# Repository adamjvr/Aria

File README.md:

# Aria
ARM Cortex M4F + WiFi + MPPT Solar Battery Powered module, mBed and Arduino Compatible hardware development platform.
- ARM Cortex M4F 180MHZ STM32F446RET6
- ESP8285 WiFi SoC w/ PCB Antenna
- WiFi
- USB 2.0 Connectivity
- Plenty or GPIO/Serial via the STM32
- Over the air programming and updating
- Lithium Ion Battery Power
- MPPT Solar battery charging
- USB bus power for desktop development
- Over the Air Programming
- Low power
- 2 Year Battery Life w/Single Cell Lithium Battery

Aria 0.1a PCB

Aria 0.1a 3D Render of PCB
Top

Bottom

Aria 0.1a ESP-12E Version PCB

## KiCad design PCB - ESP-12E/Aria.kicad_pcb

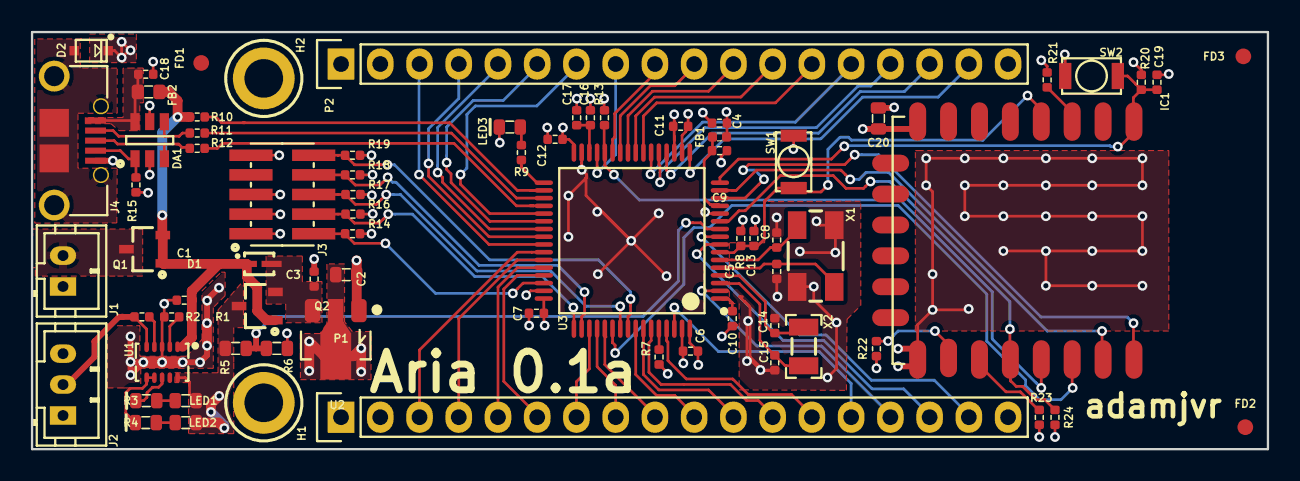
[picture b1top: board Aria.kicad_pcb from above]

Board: 4 copper layers, 80.0 x 27.0 mm, 73 parts (0 on the bottom side), 76 nets.

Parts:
C1, C2: CL05A105KA5NQNC; C0402
C3, C20: CL10A106KQ8NNNC; C0603
C4, C6, C7, C9, C10, C11, C12, C13, C17, C18, C19: CL05B104JP5NNNC; C0402
C5, C8: CL05C090CB5NNNC; C0402
C14, C15: CL05C180GB5NCNC; C0402
C16: CL05A475KQ5NRNC; C0402
D1: BAT20JFILM
D2: RSB39VTE-17
DA1: ESDA6V1BC6
FB1: BLM15HG601SN1D
FB2: MI0603K300R-10
FD1, FD2, FD3: FIDUCIAL
H1, H2: M2.5_Hole; M2.5_HOLE
IC1: ESP_12E; ESP-12E
J1: B2B-PH-K-S(LF)(SN)
J2: B3B-PH-K-S(LF)(SN)
J3: 20021121-00010C4LF
J4: 0475890001-MicroUSBPort; 0475890001
LED1: LTST-C191KGKT; LED0603
LED2: LTST-C191KFKT; LED0603
LED3: LTST-C193TBKT-5A; LED0603
P1, P2: CONN_01X18; Socket_Strip_Straight_1x18
Q1, Q2: DMG2307L-7
R1: RC1005F4870CS; R0402
R2, R8, R9, R14, R16, R17, R18, R19, R20: RC1005F102CS; R0402
R3, R4: RC1608J202CS; R0603
R5, R6: ERA-3AEB3741V; R0603
R7, R10, R13, R21, R22, R23, R24: RC1005F103CS; R0402
R11, R12: CPF0402B22RE1; R0402
R15: RC1005J473CS; R0402
SW1, SW2: B3U-1000P
U1: BQ24210DQCT; BQ24210
U2: AZ1117CR-3.3TRG1_1; AZ1117CR-3.3TRG1
U3: STM32F446RET6_-_TQFP64; STM32F446RET6
X1: ABM3B8.000MHZB2T
X2: ABS07-32.768KHZ-9-T

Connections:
+3V3: C3.1, C4.1, C6.1, C7.1, C10.1, C11.1, C12.1, C20.1, FB1.1, IC1.8, J3.1, P1.2, P2.2, R8.1, R13.1, R14.1, R16.1, R17.1, R18.1, R19.1, R20.1, R21.1, R23.1, R24.1, U2.2, U3.1, U3.19, U3.32, U3.48, U3.64
/MCU_STM32F446RET6/BAT_VOLT: R5.2, R6.1, U3.10
/MCU_STM32F446RET6/ESPTOST_BOOT0: IC1.20, U3.54
/MCU_STM32F446RET6/ESPTOST_BOOT1: IC1.19, R13.2, U3.28
/MCU_STM32F446RET6/ESP_PGM_MODE: IC1.18, R24.2, U3.11
/MCU_STM32F446RET6/ESP_ST_RST: C13.1, IC1.4, R8.2, SW1.1, U3.7
/MCU_STM32F446RET6/ESP_URX: IC1.22, U3.14
/MCU_STM32F446RET6/ESP_UTX: IC1.21, U3.15
/MCU_STM32F446RET6/HEARTBEAT: R9.1, U3.33
/MCU_STM32F446RET6/NJTRST: J3.10, R19.2, U3.56
/MCU_STM32F446RET6/PA3: P2.17, U3.17
/MCU_STM32F446RET6/PA4: P2.16, U3.20
/MCU_STM32F446RET6/PA5: P2.15, U3.21
/MCU_STM32F446RET6/PA6: P2.14, U3.22
/MCU_STM32F446RET6/PA7: P2.13, U3.23
/MCU_STM32F446RET6/PA8: P2.3, U3.41
/MCU_STM32F446RET6/PA9: P1.3, U3.42
/MCU_STM32F446RET6/PA10: P1.4, U3.43
/MCU_STM32F446RET6/PA11: P1.5, U3.44
/MCU_STM32F446RET6/PA12: P1.6, U3.45
/MCU_STM32F446RET6/PB0: P2.10, U3.26
/MCU_STM32F446RET6/PB1: P2.9, U3.27
/MCU_STM32F446RET6/PB5: P1.10, U3.57
/MCU_STM32F446RET6/PB6: P1.11, U3.58
/MCU_STM32F446RET6/PB7: P1.12, U3.59
/MCU_STM32F446RET6/PB8: P1.13, U3.61
/MCU_STM32F446RET6/PB9: P1.14, U3.62
/MCU_STM32F446RET6/PB10: P2.8, U3.29
/MCU_STM32F446RET6/PC0: P1.16, U3.8
/MCU_STM32F446RET6/PC1: P1.17, U3.9
/MCU_STM32F446RET6/PC4: P2.12, U3.24
/MCU_STM32F446RET6/PC5: P2.11, U3.25
/MCU_STM32F446RET6/PC6: P2.7, U3.37
/MCU_STM32F446RET6/PC7: P2.6, U3.38
/MCU_STM32F446RET6/PC8: P2.5, U3.39
/MCU_STM32F446RET6/PC9: P2.4, U3.40
/MCU_STM32F446RET6/PC10: P1.7, U3.51
/MCU_STM32F446RET6/PC11: P1.8, U3.52
/MCU_STM32F446RET6/PC12: P1.9, U3.53
/MCU_STM32F446RET6/PC13: P1.15, U3.2
/MCU_STM32F446RET6/STM_ESP_RST: C19.1, IC1.1, R20.2, SW2.2, U3.16
/MCU_STM32F446RET6/SWCLK_TCK: J3.4, R16.2, U3.49
/MCU_STM32F446RET6/SWDIO_TMS: J3.2, R14.2, U3.46
/MCU_STM32F446RET6/SWO_TDI: J3.8, R18.2, U3.50
/MCU_STM32F446RET6/SWO_TDO: J3.6, R17.2, U3.55
/MCU_STM32F446RET6/VBUS: C1.1, D1.1, FB2.1, Q1.1, Q1.2, Q2.1, R10.2, U1.1
/Power/BAT: J2.3, Q2.3, R3.2, R4.2, R5.1, U1.10
/Power/THERM: J2.2, R2.2, U1.5
GND: C1.2, C2.2, C3.2, C4.2, C5.2, C6.2, C7.2, C8.2, C9.2, C10.2, C11.2, C12.2, C13.2, C14.2, C15.2, C16.2, C17.2, C18.1, C19.2, C20.2, D2.2, DA1.2, DA1.5, IC1.15, J1.1, J2.1, J3.3, J3.5, J3.9, J4.5, LED3.2, P1.1, P1.18, P2.1, P2.18, R1.2, R6.2, R7.2, R15.2, R22.2, SW1.2, SW2.1, U1.3, U1.11, U2.1, U3.12, U3.18, U3.31, U3.47, U3.63, X1.2, X1.4
unnamed: C2.1, D1.2, Q2.2, U2.3
unnamed: C5.1, U3.5, X1.1
unnamed: C8.1, U3.6, X1.3
unnamed: C9.1, FB1.2, U3.13
unnamed: C14.1, U3.4, X2.1
unnamed: C15.1, U3.3, X2.2
unnamed: C16.1, C17.1, U3.30
unnamed: C18.2, DA1.6, FB2.2, J4.1
unnamed: D2.1, J4.6, J4.7, J4.8, J4.9, J4.10, J4.11
unnamed: DA1.1, J4.4, R15.1
unnamed: DA1.3, J4.3, R12.2
unnamed: DA1.4, J4.2, R11.2
unnamed: IC1.3, R21.2
unnamed: IC1.16, R22.1
unnamed: IC1.17, R23.2
unnamed: J1.2, Q1.3
unnamed: LED1.1, R3.1
unnamed: LED1.2, U1.8
unnamed: LED2.1, R4.1
unnamed: LED2.2, U1.6, U1.7
unnamed: LED3.1, R9.2
unnamed: R1.1, U1.2
unnamed: R2.1, U1.4
unnamed: R7.1, U3.60
unnamed: R10.1, U3.34
unnamed: R11.1, U3.35
unnamed: R12.1, U3.36

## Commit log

2016-09-27 Specs
    Simple Specs Added
2016-09-27 Schematic
    Schematic 90% complete, and Board layout started. Next update schematic
    should be solidified and board layout near complete.
2016-09-29 License
    CERN Open Hardware License Added
2016-09-29 Board Layout
    Board layout started. ESP8285 component placement preliminary complete.
    3D parts added and updated for ESP8285. STM32 and SOT32 3/6 pin
    packages.
2016-09-29 Preliminary Formfactor
    Preliminary formfactor designed. component placelement still underway
2016-09-29 Finished Placement and Mapping
    Components placed, some routing completed. pin header mapping figured
    out.
2016-09-30 Layout
    layout underway, one side completely routed, next other side, ESP, and
    PCB antenna. Added PDF for app not on 2.4GHZ antenna similar to the one
    sparkfun uses in their thing boards, I suspect this is where they got it
    and it seems reliable.
2016-10-02 Board Size. Routing and Antenna
    Board Size tweaked. More signals routed. Next will be pin swapping and
    routing finished. Also experimented with importing a PCB antenna design
    from bitmap, still can't get it quite right, hopefully nex commit.
2016-10-04 More routing
    more routing completed, but thinking of scraping the current pass
    entirely and rechoosing all the pins.
2016-10-13 Updates
    Changed board size, heavily altered schematic and pinning to be more
    efficient. Program mode for ESP8285 is switched to GPIO0 being pulled
    high 10k and toggled by STM32. Board at 30mm By 70.5mm. Also switching
    to chip antenna next commit, expect updates to libraries.
2016-10-14 Board Finished
    Board finished
2016-10-14 Readme
    Readme updated
2016-10-16 ESP Footprint Error and RF improvement
    ESP8285 footprint was wrong, made when I was still learning kiCAD.
    Footprint change and entire topology reconstructed and rerouted. Added
    ground pours and heavy via stitching to improve RF performance. Also
    started an ESP-12E module based variant. Both will be fabbed at the same
    time.
2016-10-18 DRC Cleared and Pictures
    DRC cleared of errors for both Aria board designs. New pictures have
    been added. Readme has also been updated.
2016-10-18 Removed Renders
    Removed OSHPark renders
2016-10-18 Added to Readme
    Added to Readme
2016-10-18 Changes
    more readme changes
2016-10-27 Switch
    Power switch added for switching board off for storage and shipping.
    Power supply circuit routing revised and updated.
2016-10-29 Power Switch Revision
    Power switch and power supply topology revised. New microchip LDO from
    Ventor replaces old LDO, power switch not toggles LDO shutdown enable
    for turing Aria on and off.
